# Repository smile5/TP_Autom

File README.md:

# TP_Autom

CAo + Code TP_Autom

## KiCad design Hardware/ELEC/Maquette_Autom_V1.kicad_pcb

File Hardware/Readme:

Ici se trouve les fichiers CAO Elec et Meca

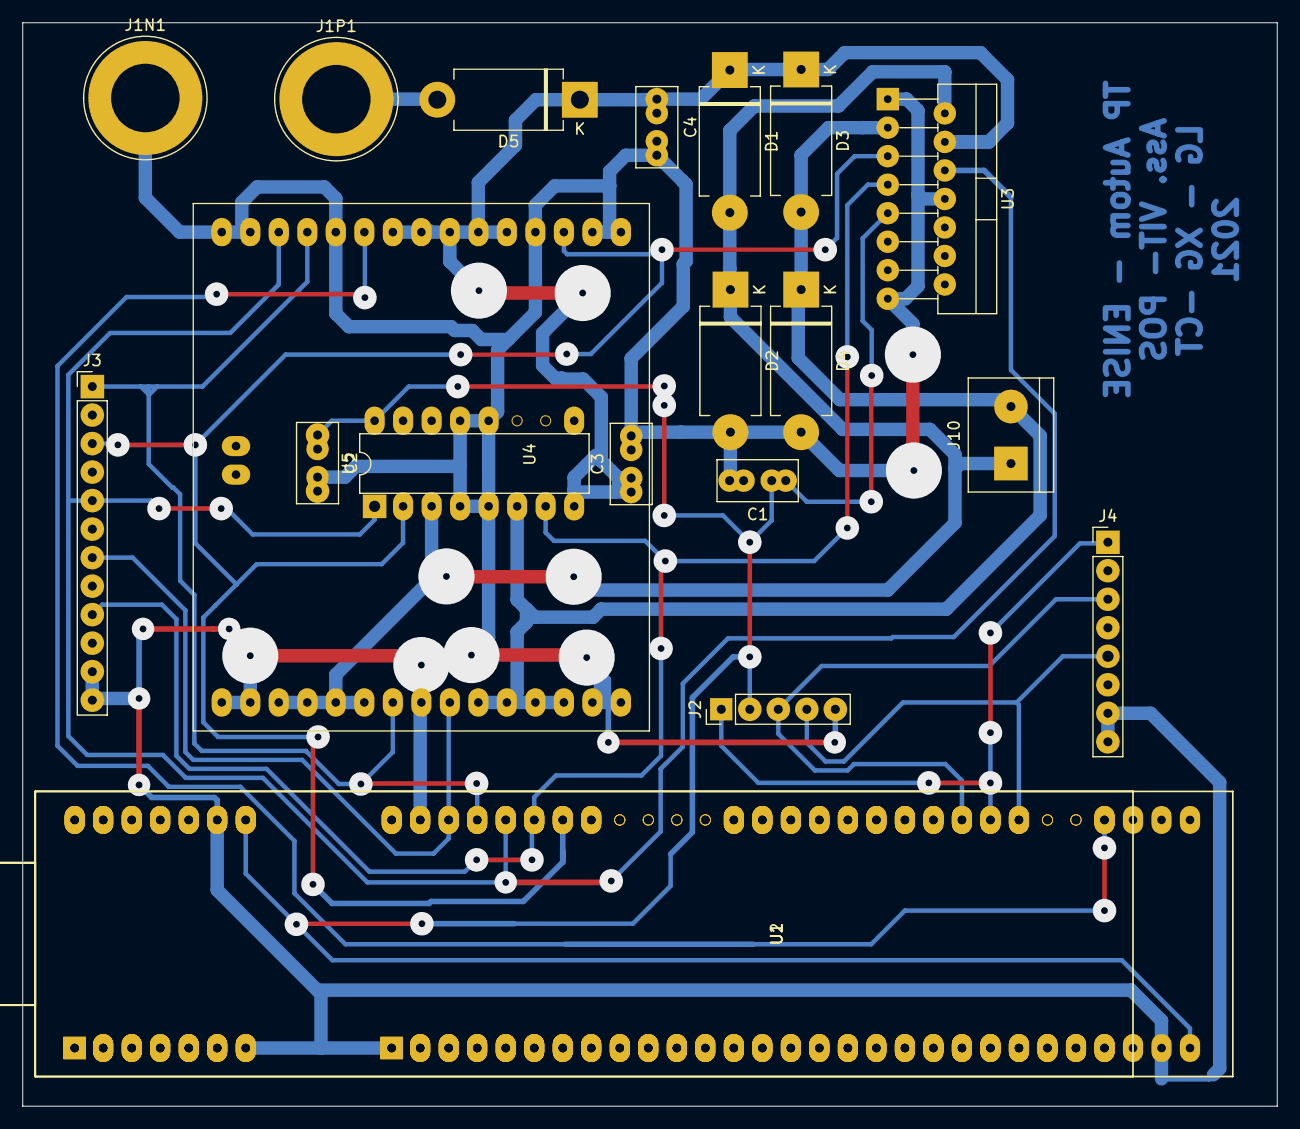
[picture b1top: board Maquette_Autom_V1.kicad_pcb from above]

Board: 2 copper layers, 111.8 x 96.5 mm, 20 parts (0 on the bottom side), 15 nets.

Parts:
C1, C2, C3, C4: C; C_Rect_L7.0mm_W3.5mm_P2.50mm_P5.00mm
D1, D2, D3, D4, D5: MBR360; D_DO-201AD_P12.70mm_Horizontal
J1N1, J1P1: Conn_01x01; Banana_Jack_1Pin
J2: Conn_01x05; PinHeader_1x05_P2.54mm_Vertical
J3: Conn_01x012; PinHeader_1x12_P2.54mm_Vertical
J4: Conn_01x08; PinHeader_1x08_P2.54mm_Vertical
J10: Screw_Terminal_01x02; TerminalBlock_bornier-2_P5.08mm
U1: Cy8ckit-059
U2: Cy8ckit-043
U3: L298HN; TO-220-15_P2.54x2.54mm_StaggerOdd_Lead4.58mm_Vertical
U4: ev-vnh7040ay
U5: L293D; DIP-16_W7.62mm

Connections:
/5_V: C1.1, C2.1, J2.2, U1.Kp8, U2.29, U2.Kp8, U3.9, U5.16
/CH_A: J2.1, J4.1, U1.31, U2.37
/CH_B: J2.3, J4.3, U1.32, U2.38
/CH_I: J2.4, J4.5, U1.30, U2.36
/Enable: J3.5, U1.48, U2.54, U3.6, U4.28, U5.1
/INA: J3.1, U1.49, U2.55, U4.7, U4.27
/INB: J3.7, U1.50, U2.56, U4.9
/I_Sense: U1.27, U2.33, U4.25
/M1+: D1.2, D2.1, J10.1, U3.2, U4.3, U5.3
/M1-: D3.2, D4.1, J10.2, U3.3, U4.10, U5.6
/PwmA: J3.3, U1.46, U2.52, U3.5, U4.18, U5.2
/PwmB: J3.9, U1.47, U2.53, U3.7, U5.7
/Vmot: C3.1, C4.1, D1.1, D3.1, D5.1, U3.4, U4.20, U4.22, U5.8
GNDPWR: C1.2, C2.2, C3.2, C4.2, D2.2, D4.2, J1N1.1, J2.5, J3.11, J3.12, J4.7, J4.8, U1.1, U1.51, U1.Kp7, U1.Kp9, U2.1, U2.28, U2.57, U2.Kp7, U2.Kp9, U3.1, U3.8, U3.15, U4.1, U4.15, U4.19, U5.4, U5.5, U5.12, U5.13
unnamed: D5.2, J1P1.1

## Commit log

2021-06-04 Create CAO
2021-06-04 Create none
2021-06-04 Create Software
